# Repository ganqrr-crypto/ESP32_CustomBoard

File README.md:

# ESP32_CustomBoard
IMPORTANT NOTES FOR REVIEWER: Go read the file i am saying "reviewer read this" if you are questioning why you see all journals work session. 
anyways if you don't want to read it and i respect it, says that i am using timelapses and not journals. Have a good day!

This is a ESP32 custom board project that i made/i am making for Half Life by Hack club 

This Board uses the ESP32-S3-WROOM1-N8 as the microcontroller and it  featuresan app on windows that lets you turn on a led and off..

It features a enclosure too

BOM:
BOM can be found in the folder "Manufacturing"
## Bill of Materials (BOM)

| Component | Purpose | Qty | Cost (USD) | Vendor | Link |
|---|---|---:|---:|---|---|
| 10 µF Tantalum Capacitor | Capacitors | 2 | $0.78 | TME | [Product page](https://www.tme.eu/it/details/t491a106k006at/condensatori-di-tantalio-smd/kemet/) |
| 22 µF Tantalum Capacitor | Capacitors | 2 | $1.01 | TME | [Product page](https://www.tme.eu/it/details/t491a226k006at/condensatori-di-tantalio-smd/kemet/) |
| ESP32-S3-WROOM-1-N8 | Microcontroller | 1 | $5.30 | TME | [Product page](https://www.tme.eu/it/details/esp32s3-wrm1-8/moduli-iot-wifi-bluetooth/espressif/esp32-s3-wroom-1-n8/) |
| 0.1 µF Capacitor | Capacitors | 3 | $0.26 | TME | [Product page](https://www.tme.eu/it/details/0805b104k500ct/condensatori-mlcc-smd/walsin/) |
| LED | Power LED | 3 | $0.40 | TME | [Product page](https://www.tme.eu/it/details/ltst-c171kgkt/diodi-led-smd-colorati/liteon/) |
| USB-C Port | USB Port | 1 | $1.46 | TME | [Product page](https://www.tme.eu/it/details/usb4085-gf-a/connettori-usb-e-ieee-1394/gct/) |
| 4-Pin Connector | Pins | 10 | $1.89 | TME | [Product page](https://www.tme.eu/it/details/ds1002-01-1x04v13/connettore-dell-intestazione-di-pin/connfly/ds1002-01-1-4v13-jk/) |
| 6-Pin Connector | Pins | 10 | $2.00 | TME | [Product page](https://www.tme.eu/it/details/ds1002-01-1x06v13/connettore-dell-intestazione-di-pin/connfly/ds1002-01-1-6v13/) |
| 5.1 kΩ Resistors | Resistors | 10 | $0.35 | TME | [Product page](https://www.tme.eu/it/details/rc0805fr-075k1/resistori-smd/yageo/rc0805fr-075k1l/) |
| 10 kΩ Resistors | Resistors | 10 | $0.81 | TME | [Product page](https://www.tme.eu/it/details/pwr0805-10k-1%25/resistori-smd/viking/pwr05ftew1002/) |
| Tactile Buttons | RESET and BOOT | 2 | $0.40 | TME | [Product page](https://www.tme.eu/it/details/tl3305af160qg/microinterruttori-tact/e-switch/) |
| ESD Protection | ESD protection | 1 | $0.27 | TME | [Product page](https://www.tme.eu/it/details/usblc6-2sc6-aks/diodi-di-protezione-reti/akyga-semi/aks1201/) |
| 3.3 V Regulator | 3.3 V regulation | 1 | $0.36 | TME | [Product page](https://www.tme.eu/it/details/ld1117as33tr/stabilizzatori-di-tens-non-regol-ldo/stmicroelectronics/) |
| PCB | Printed circuit board | 5 | $3.93 | JLCPCB | [JLCPCB](https://jlcpcb.com/) |

### Cost Summary

| Item | Cost (USD) |
|---|---:|
| Shipping | $22.00 |
| Taxes | $18.77 |
| **Total Components + Shipping** | **$51.67** |

Schematics:

Model: 

PCB :

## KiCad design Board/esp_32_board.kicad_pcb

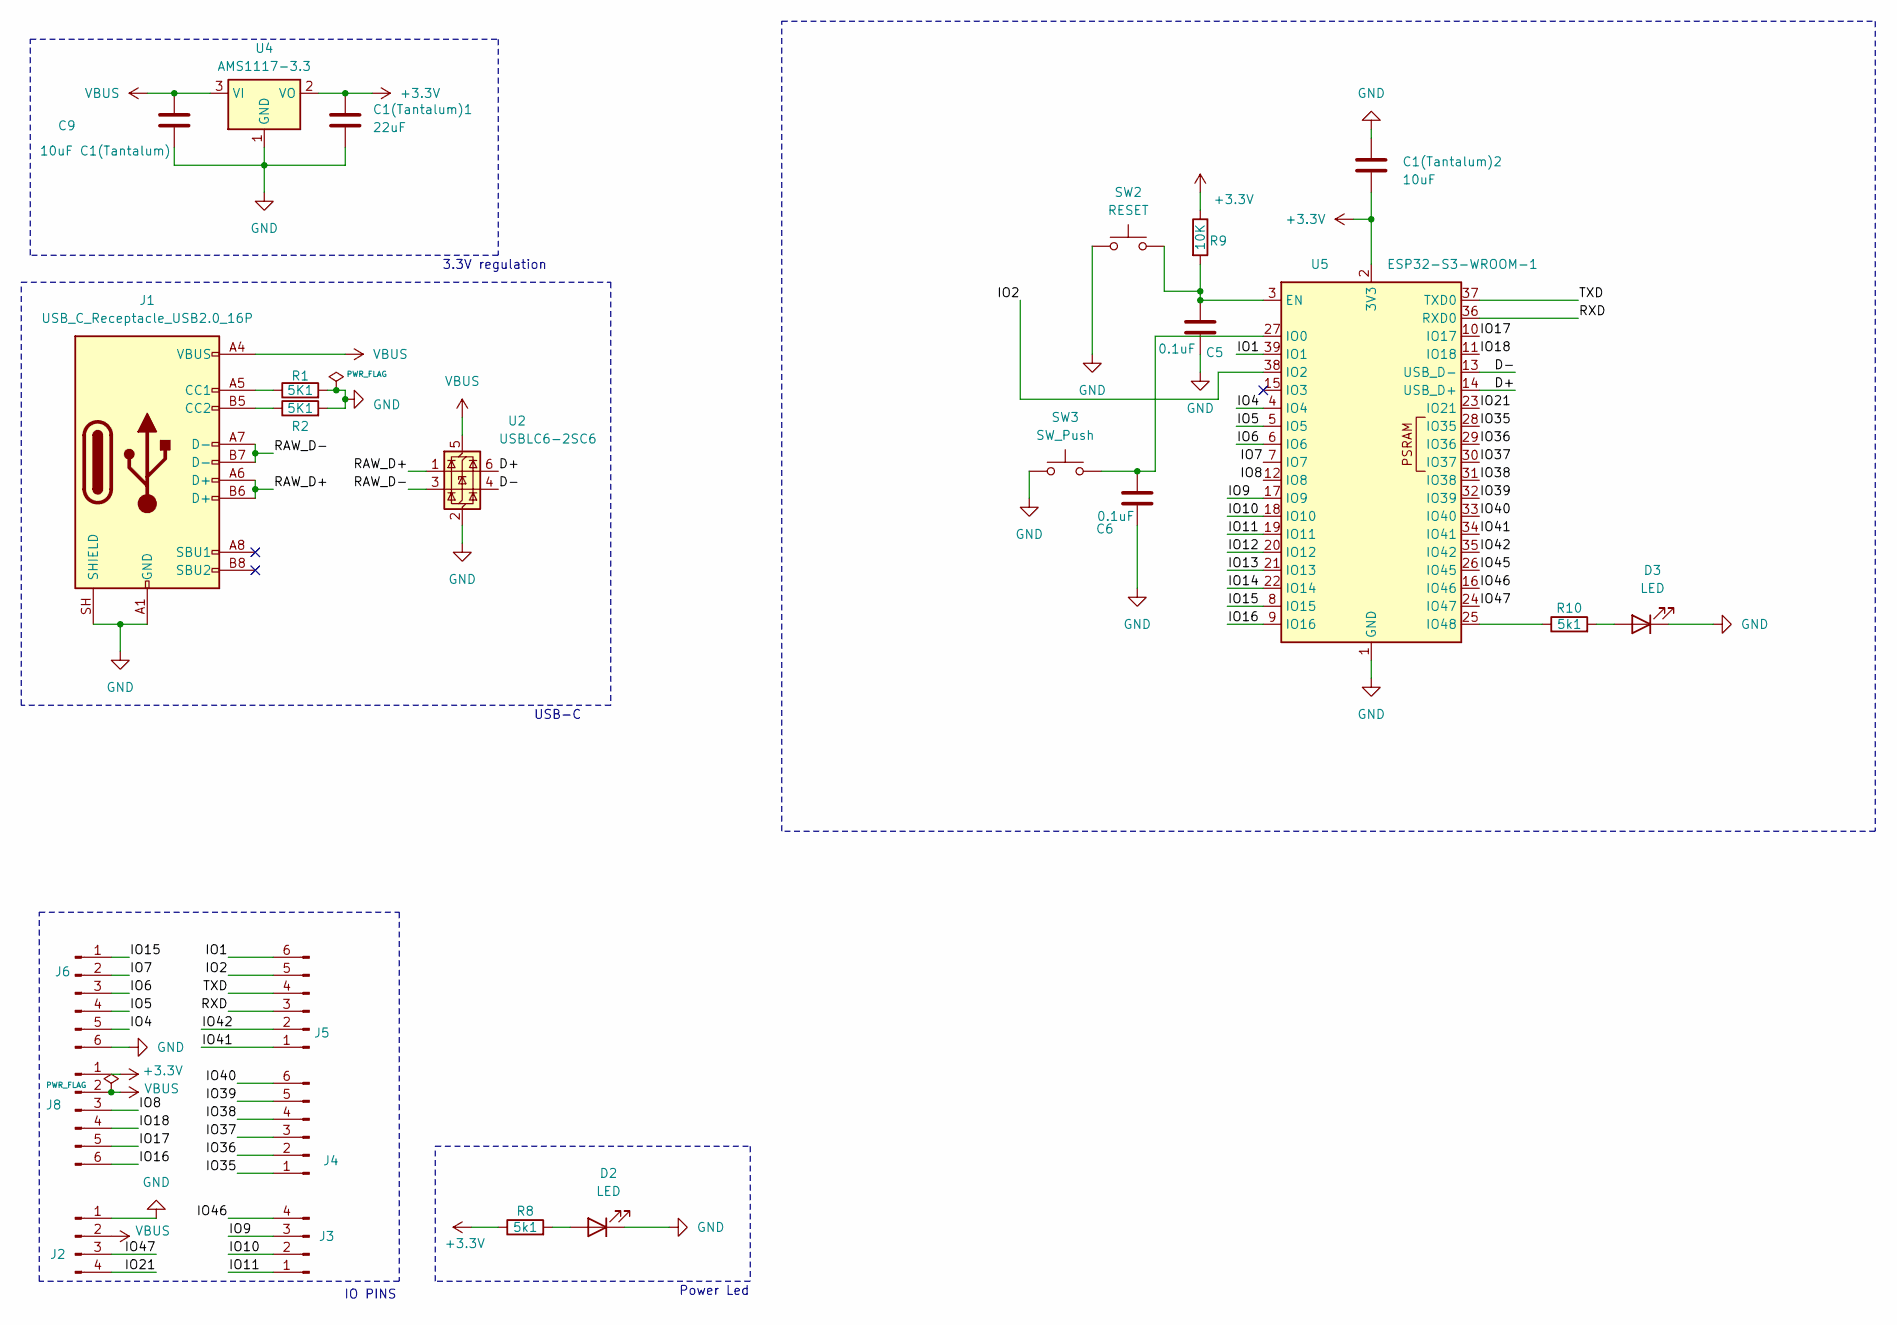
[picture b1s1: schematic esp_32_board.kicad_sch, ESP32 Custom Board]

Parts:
C1(Tantalum)1: 22uF; CP_EIA-3216-18_Kemet-A_HandSolder
C1(Tantalum)2: 10uF; CP_EIA-3216-18_Kemet-A_HandSolder
C5, C6: 0.1uF; C_0805_2012Metric_Pad1.18x1.45mm_HandSolder
C9: 10uF C1(Tantalum); CP_EIA-3216-18_Kemet-A_HandSolder
D2, D3: LED; LED_0805_2012Metric_Pad1.15x1.40mm_HandSolder
J1: USB_C_Receptacle_USB2.0_16P; USB_C_Receptacle_GCT_USB4085
J2: UART; PinSocket_1x04_P2.54mm_Vertical
J3: JTAG; PinSocket_1x04_P2.54mm_Vertical
J4, J5, J6, J8: Conn_01x06_Pin; PinSocket_1x06_P2.54mm_Vertical
R1, R2: 5K1; R_0805_2012Metric_Pad1.20x1.40mm_HandSolder
R8, R10: 5k1; R_0805_2012Metric_Pad1.20x1.40mm_HandSolder
R9: 10K; R_0805_2012Metric_Pad1.20x1.40mm_HandSolder
SW2: RESET; SW_SPST_TL3305A
SW3: SW_Push; SW_SPST_TL3305A
U2: USBLC6-2SC6; SOT-23-6
U4: AMS1117-3.3; SOT-223-3_TabPin2
U5: ESP32-S3-WROOM-1

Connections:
+3.3V: C1(Tantalum)1.1, C1(Tantalum)2.2, J8.1, R8.1, R9.1, U4.2 (VO), U5.2 (3V3)
/D+: U2.6 (I/O1), U5.14 (USB_D+)
/D-: U2.4 (I/O2), U5.13 (USB_D-)
/IO1: J5.6, U5.39 (IO1)
/IO2: J5.5, U5.38 (IO2)
/IO4: J6.5, U5.4 (IO4)
/IO5: J6.4, U5.5 (IO5)
/IO6: J6.3, U5.6 (IO6)
/IO7: J6.2, U5.7 (IO7)
/IO8: J8.3, U5.12 (IO8)
/IO9: J3.3, U5.17 (IO9)
/IO10: J3.2, U5.18 (IO10)
/IO11: J3.1, U5.19 (IO11)
/IO12: U5.20 (IO12)
/IO13: U5.21 (IO13)
/IO14: U5.22 (IO14)
/IO15: J6.1, U5.8 (IO15)
/IO16: J8.6, U5.9 (IO16)
/IO17: J8.5, U5.10 (IO17)
/IO18: J8.4, U5.11 (IO18)
/IO21: J2.4, U5.23 (IO21)
/IO35: J4.1, U5.28 (IO35)
/IO36: J4.2, U5.29 (IO36)
/IO37: J4.3, U5.30 (IO37)
/IO38: J4.4, U5.31 (IO38)
/IO39: J4.5, U5.32 (IO39)
/IO40: J4.6, U5.33 (IO40)
/IO41: J5.1, U5.34 (IO41)
/IO42: J5.2, U5.35 (IO42)
/IO45: U5.26 (IO45)
/IO46: J3.4, U5.16 (IO46)
/IO47: J2.3, U5.24 (IO47)
/RAW_D+: J1.A6 (D+), J1.B6 (D+), U2.1 (I/O1)
/RAW_D-: J1.A7 (D-), J1.B7 (D-), U2.3 (I/O2)
/RXD: J5.3, U5.36 (RXD0)
/TXD: J5.4, U5.37 (TXD0)
GND: C1(Tantalum)1.2, C1(Tantalum)2.1, C5.1, C6.1, C9.2, D2.1 (K), D3.1 (K), J1.A1 (GND), J1.A12 (GND), J1.B1 (GND), J1.B12 (GND), J1.SH (SHIELD), J2.1, J6.6, R1.2, R2.2, SW2.1, SW3.1, U2.2 (GND), U4.1 (GND), U5.1 (GND), U5.40 (GND), U5.41 (GND)
unnamed: D2.2 (A), R8.2
unnamed: D3.2 (A), R10.2
unnamed: J1.A5 (CC1), R1.1
unnamed: J1.B5 (CC2), R2.1
unnamed: C5.2, R9.2, SW2.2, U5.3 (EN)
unnamed: C6.2, SW3.2, U5.27 (IO0)
unnamed: R10.1, U5.25 (IO48)
VBUS: C9.1, J1.A4 (VBUS), J1.A9 (VBUS), J1.B4 (VBUS), J1.B9 (VBUS), J2.2, J8.2, U2.5 (VBUS), U4.3 (VI)

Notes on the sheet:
3.3V regulation
IO PINS
Power Led
USB-C

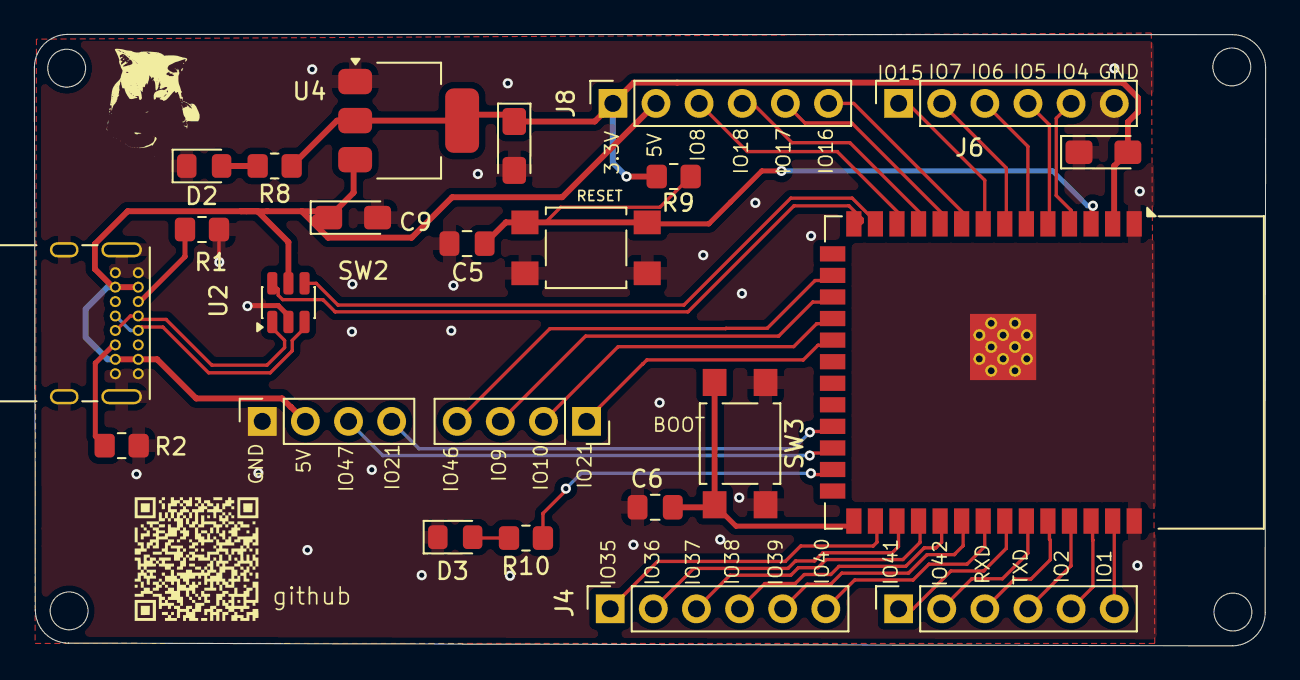
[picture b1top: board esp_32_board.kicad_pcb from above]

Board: 2 copper layers, 72.5 x 36.0 mm, 24 parts (0 on the bottom side), 41 nets.
